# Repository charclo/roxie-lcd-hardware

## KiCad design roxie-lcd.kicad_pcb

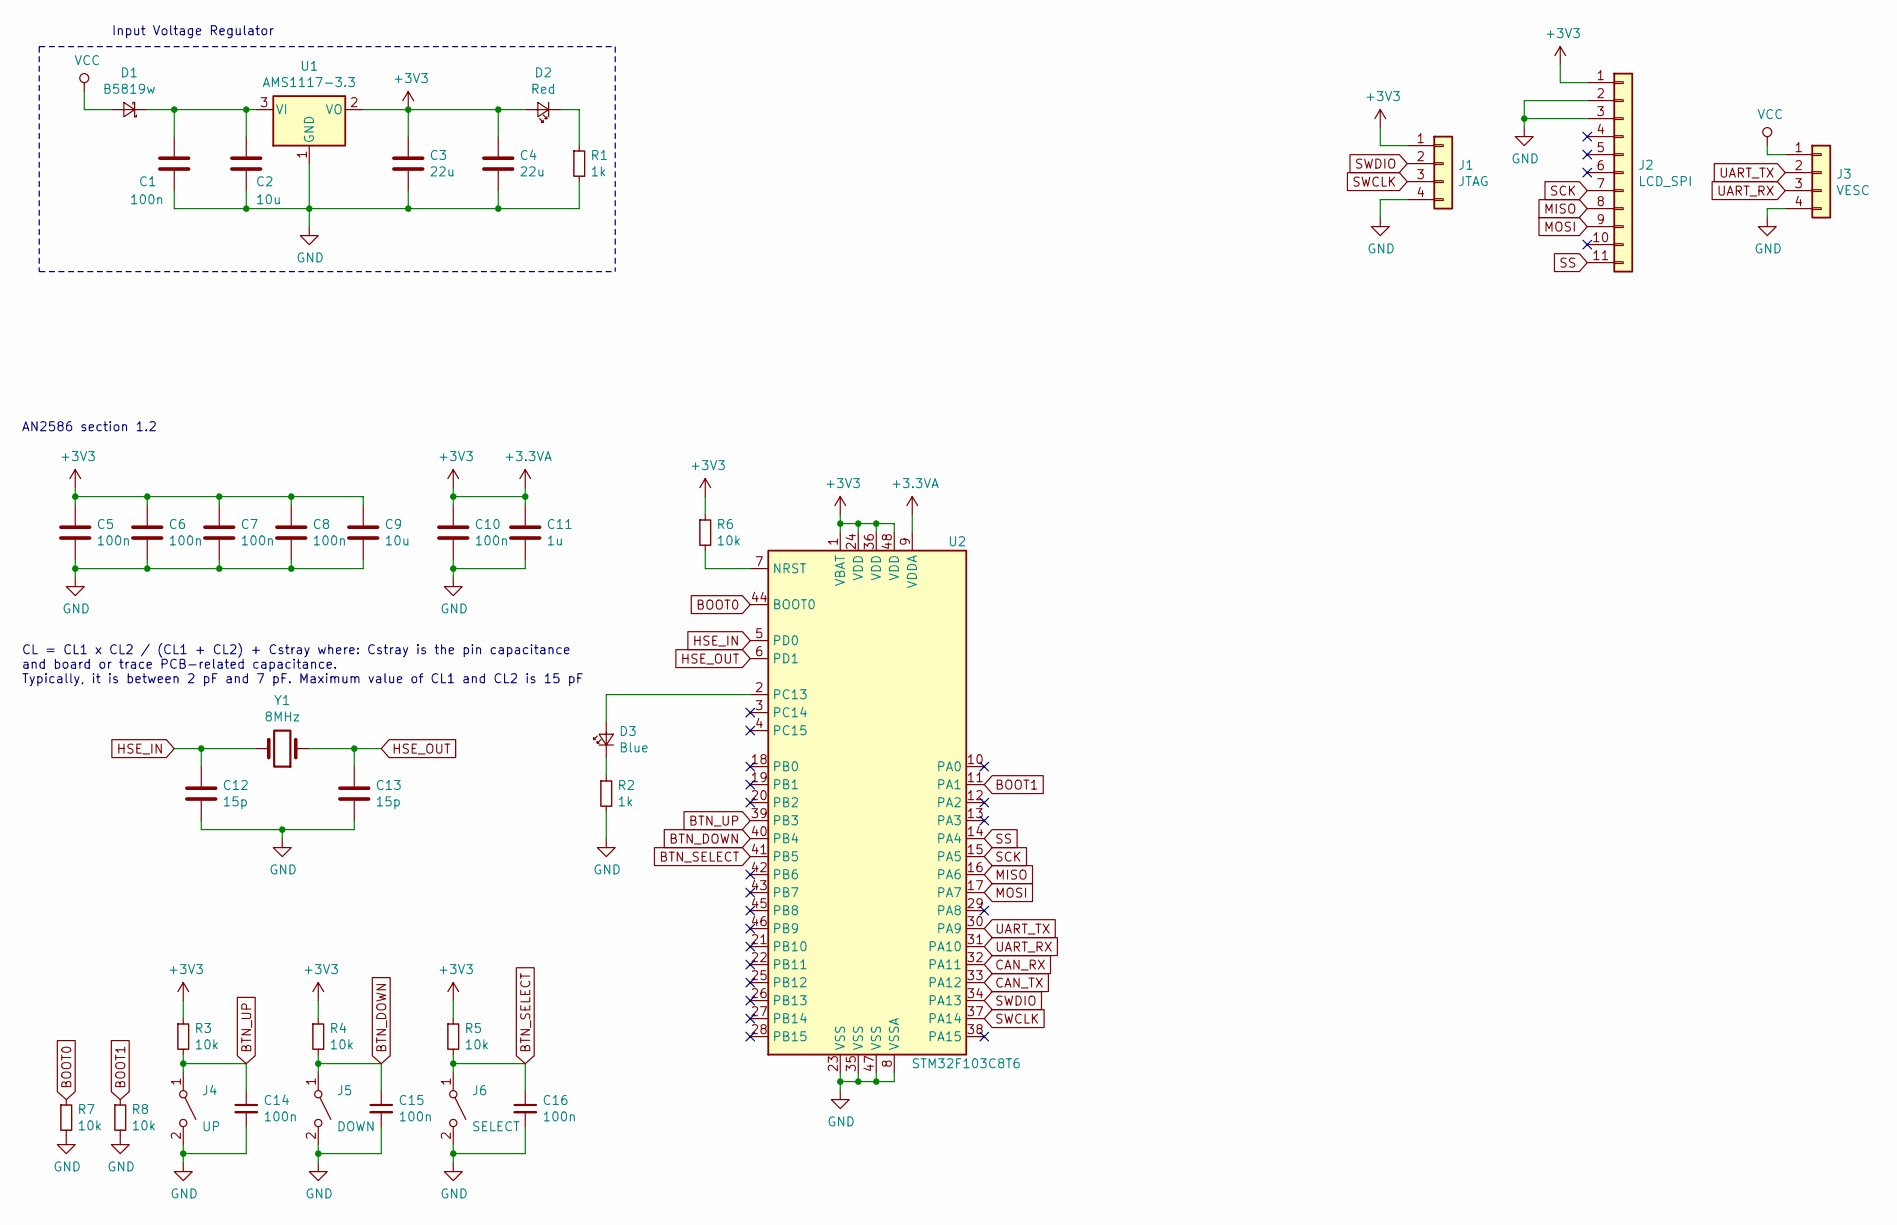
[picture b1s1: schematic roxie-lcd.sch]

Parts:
C1, C5, C6, C7, C8, C10, C14, C15, C16: 100n; C_0402_1005Metric
C2, C9: 10u; C_0805_2012Metric
C3, C4: 22u; C_0805_2012Metric
C11: 1u; C_0603_1608Metric
C12, C13: 15p; C_0402_1005Metric
D1: B5819w; D_SOD-123
D2: Red; LED_0603_1608Metric
D3: Blue; LED_0603_1608Metric
J1: JTAG; PinHeader_1x04_P2.54mm_Horizontal
J2: LCD_SPI; PinHeader_1x11_P2.54mm_Vertical
J3: VESC; JST_PH_S4B-PH-K_1x04_P2.00mm_Horizontal
J4: UP; PinHeader_1x02_P2.54mm_Vertical
J5: DOWN; PinHeader_1x02_P2.54mm_Vertical
J6: SELECT; PinHeader_1x02_P2.54mm_Vertical
R1, R2: 1k; R_0603_1608Metric
R3, R4, R5, R6, R7, R8: 10k; R_0603_1608Metric
U1: AMS1117-3.3; SOT-223-3_TabPin2
U2: STM32F103C8T6; LQFP-48_7x7mm_P0.5mm
Y1: 8MHz; Crystal_SMD_5032-2Pin_5.0x3.2mm

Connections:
+3.3VA: C3.1, C4.1, C5.1, C6.1, C7.1, C8.1, C9.1, C10.1, C11.1, D2.2 (A), J1.1, J2.1, R3.1, R4.1, R5.1, R6.1, U1.2 (VO), U2.1 (VBAT), U2.9 (VDDA), U2.24 (VDD), U2.36 (VDD), U2.48 (VDD)
BOOT0: R7.1, U2.44 (BOOT0)
BOOT1: R8.1, U2.11 (PA1)
BTN_DOWN: C15.1, J5.1 (A), R4.2, U2.40 (PB4)
BTN_SELECT: C16.1, J6.1 (A), R5.2, U2.41 (PB5)
BTN_UP: C14.1, J4.1 (A), R3.2, U2.39 (PB3)
CAN_RX: U2.32 (PA11)
CAN_TX: U2.33 (PA12)
GND: C1.2, C2.2, C3.2, C4.2, C5.2, C6.2, C7.2, C8.2, C9.2, C10.2, C11.2, C12.2, C13.2, C14.2, C15.2, C16.2, J1.4, J2.2, J2.3, J3.4, J4.2 (B), J5.2 (B), J6.2 (B), R1.2, R2.2, R7.2, R8.2, U1.1 (GND), U2.8 (VSSA), U2.23 (VSS), U2.35 (VSS), U2.47 (VSS)
HSE_IN: C12.1, U2.5 (PD0), Y1.2
HSE_OUT: C13.1, U2.6 (PD1), Y1.1
MISO: J2.8, U2.16 (PA6)
MOSI: J2.9, U2.17 (PA7)
unnamed: C1.1, C2.1, D1.1 (K), U1.3 (VI)
unnamed: D2.1 (K), R1.1
unnamed: D3.1 (K), R2.1
unnamed: D3.2 (A), U2.2 (PC13)
unnamed: R6.2, U2.7 (NRST)
SCK: J2.7, U2.15 (PA5)
SS: J2.11, U2.14 (PA4)
SWCLK: J1.3, U2.37 (PA14)
SWDIO: J1.2, U2.34 (PA13)
UART_RX: J3.3, U2.31 (PA10)
UART_TX: J3.2, U2.30 (PA9)
VCC: D1.2 (A), J3.1

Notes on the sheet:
Input Voltage Regulator
AN2586 section 1.2
CL = CL1 x CL2 / (CL1 + CL2) + Cstray where: Cstray is the pin capacitance and board or trace PCB-related capacitance. Typically, it is between 2 pF and 7 pF. Maximum value of CL1 and CL2 is 15 pF

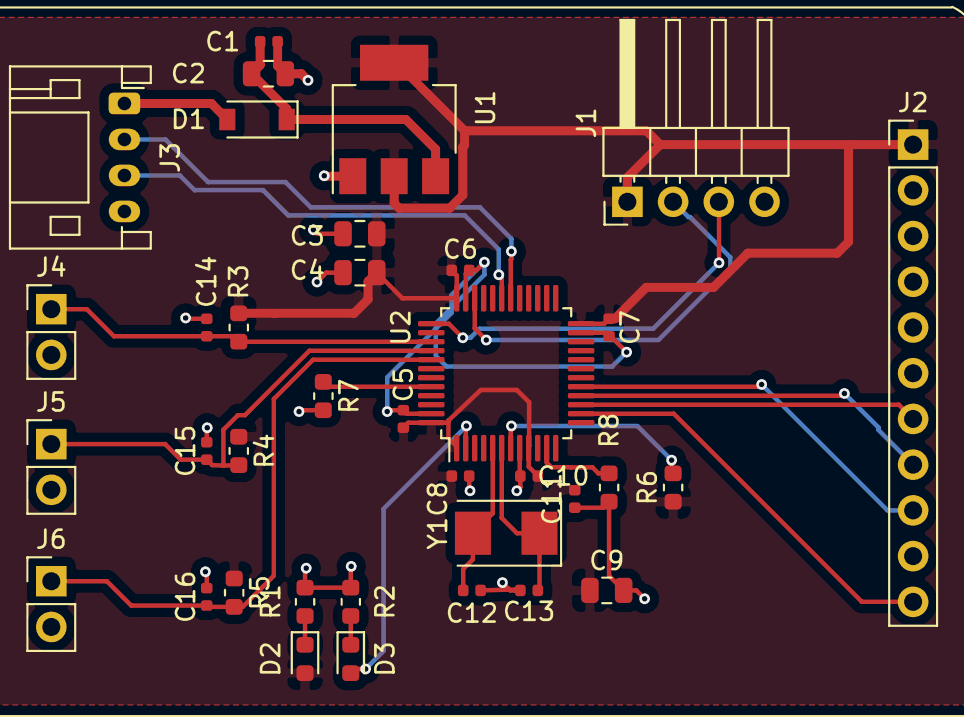
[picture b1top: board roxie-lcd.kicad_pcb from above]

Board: 2 copper layers, 36 parts (0 on the bottom side), 23 nets.

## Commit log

2020-05-26 added pdf's
2020-05-26 added pdf's again
2020-07-13 Change connectors
2020-12-07 Added lots of things
2020-12-07 Quick pcb routing
2021-03-03 new schematic
